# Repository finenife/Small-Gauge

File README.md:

# Small Gauge
 Open Source replacement for the Mazda Miata Oil Pressure Gauge 

## some small notes for myself of other repos ill be referencing
- ill likely move this away from a mono repo at some point

- Screen - ST77903 - 1.6 Inch TFT Display  LCD MODULE Circular Display 400x400 ST77903 Driver Quad-SPI Interface 14Pins
https://a.aliexpress.com/_mM0T8uA

- LVGL - https://lvgl.io/

- ESP-IDF CAN (TWAI) Library documentation
https://docs.espressif.com/projects/esp-idf/en/stable/esp32s2/api-reference/peripherals/twai.html

- RejsaCAN-ESP32 https://github.com/MagnusThome/RejsaCAN-ESP32

- ST77903 ESP Library
https://github.com/moononournation/Arduino_GFX/issues/395

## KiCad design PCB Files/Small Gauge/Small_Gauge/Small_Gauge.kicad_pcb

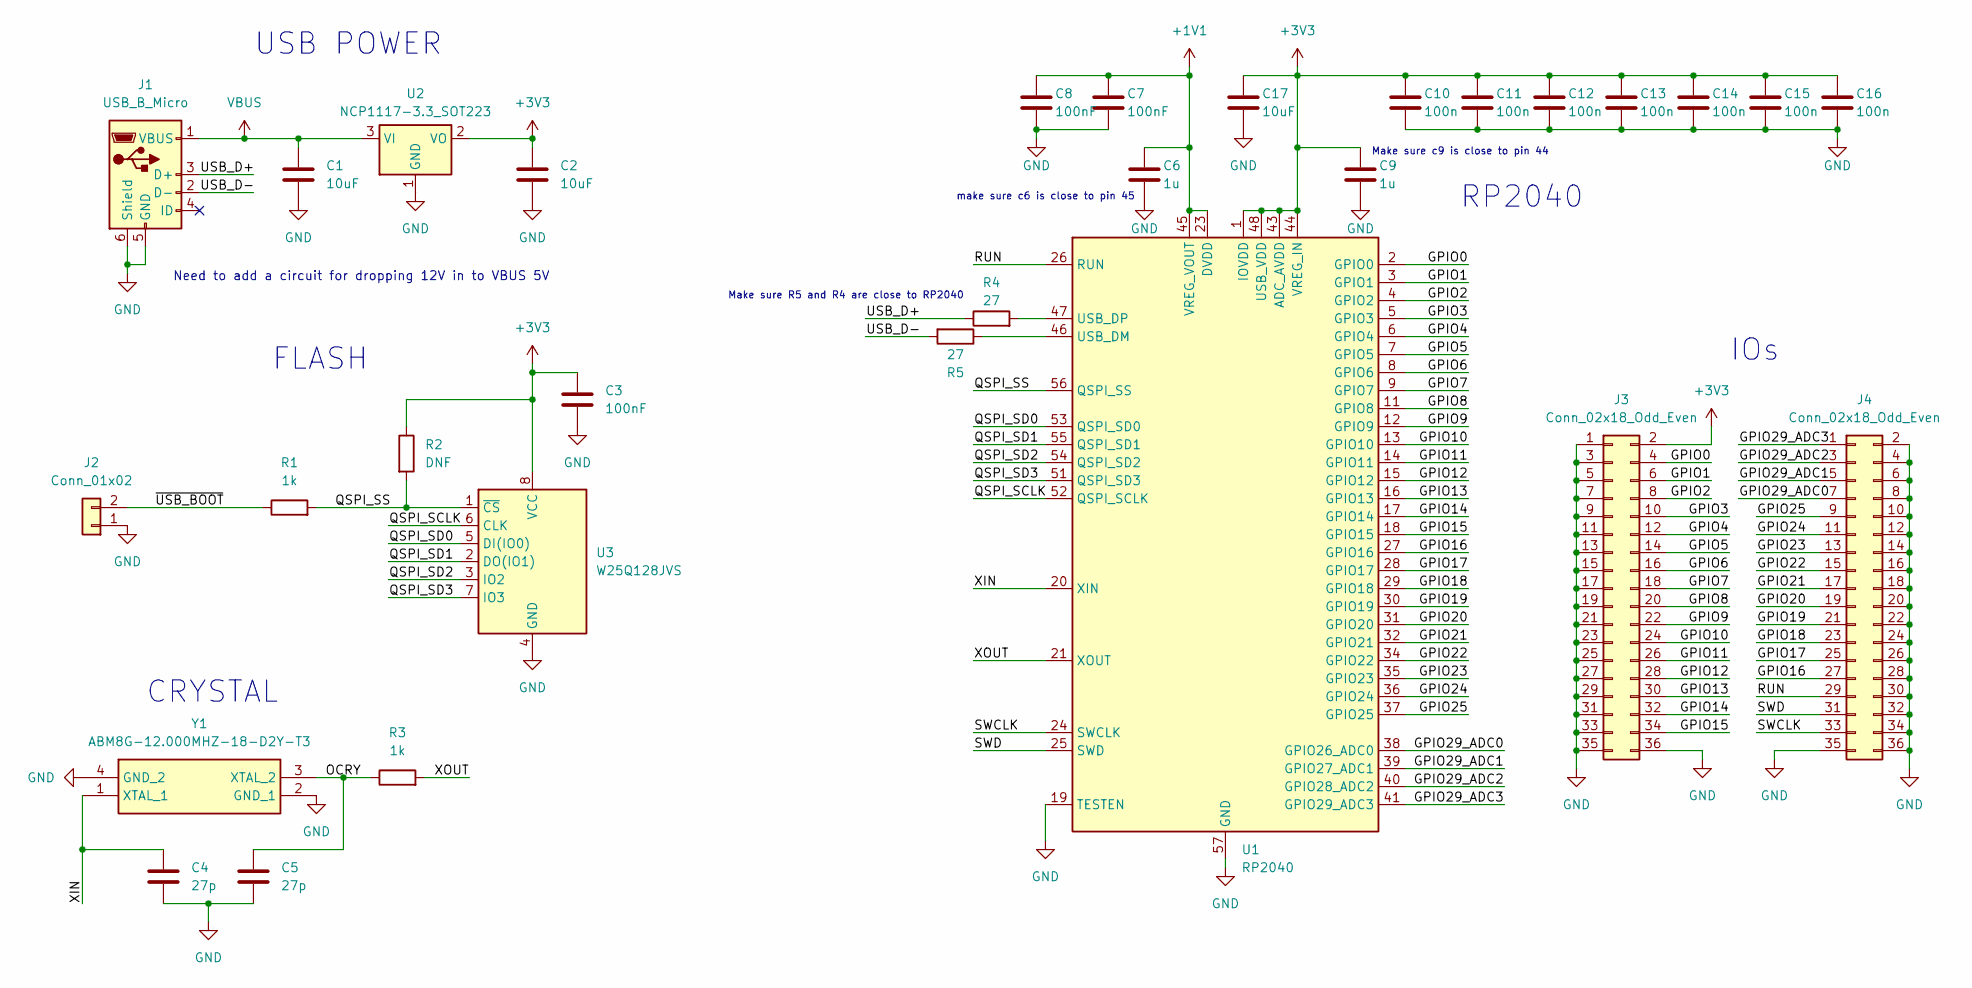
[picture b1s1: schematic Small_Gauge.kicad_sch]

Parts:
C1, C2, C17: 10uF; C_0402_1005Metric_Pad0.74x0.62mm_HandSolder
C3, C7, C8: 100nF; R_0201_0603Metric
C4, C5: 27p; C_0201_0603Metric
C6, C9: 1u; C_0201_0603Metric
C10, C11, C12, C13, C14, C15, C16: 100n; R_0201_0603Metric
J1: USB_B_Micro; USB_MICRO_B_1051640001
J2: Conn_01x02; JST_EH_B2B-EH-A_1x02_P2.50mm_Vertical
J3, J4: Conn_02x18_Odd_Even; JST_PUD_B36B-PUDSS_2x18_P2.00mm_Vertical
R1, R3: 1k; R_0201_0603Metric_Pad0.64x0.40mm_HandSolder
R2: DNF; R_0201_0603Metric_Pad0.64x0.40mm_HandSolder
R4, R5: 27; R_0402_1005Metric
U1: RP2040; QFN-56-1EP_7x7mm_P0.4mm_EP3.2x3.2mm
U2: NCP1117-3.3_SOT223; SOT-223-3_TabPin2
U3: W25Q128JVS; SOIC-8_5.23x5.23mm_P1.27mm
Y1: ABM8G-12.000MHZ-18-D2Y-T3; ABM8G; Mouser Part Number 815-ABM8G1218D2YT3

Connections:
+1V1: C6.1, C7.1, C8.1, U1.23 (DVDD), U1.45 (VREG_VOUT), U1.50 (DVDD)
+3V3: C2.1, C3.1, C9.1, C10.1, C11.1, C12.1, C13.1, C14.1, C15.1, C16.1, C17.1, J3.2, R2.1, U1.1 (IOVDD), U1.10 (IOVDD), U1.22 (IOVDD), U1.33 (IOVDD), U1.42 (IOVDD), U1.43 (ADC_AVDD), U1.44 (VREG_IN), U1.48 (USB_VDD), U1.49 (IOVDD), U2.2 (VO), U3.8 (VCC)
/GPIO0: J3.4, U1.2 (GPIO0)
/GPIO1: J3.6, U1.3 (GPIO1)
/GPIO2: J3.8, U1.4 (GPIO2)
/GPIO3: J3.10, U1.5 (GPIO3)
/GPIO4: J3.12, U1.6 (GPIO4)
/GPIO5: J3.14, U1.7 (GPIO5)
/GPIO6: J3.16, U1.8 (GPIO6)
/GPIO7: J3.18, U1.9 (GPIO7)
/GPIO8: J3.20, U1.11 (GPIO8)
/GPIO9: J3.22, U1.12 (GPIO9)
/GPIO10: J3.24, U1.13 (GPIO10)
/GPIO11: J3.26, U1.14 (GPIO11)
/GPIO12: J3.28, U1.15 (GPIO12)
/GPIO13: J3.30, U1.16 (GPIO13)
/GPIO14: J3.32, U1.17 (GPIO14)
/GPIO15: J3.34, U1.18 (GPIO15)
/GPIO16: J4.27, U1.27 (GPIO16)
/GPIO17: J4.25, U1.28 (GPIO17)
/GPIO18: J4.23, U1.29 (GPIO18)
/GPIO19: J4.21, U1.30 (GPIO19)
/GPIO20: J4.19, U1.31 (GPIO20)
/GPIO21: J4.17, U1.32 (GPIO21)
/GPIO22: J4.15, U1.34 (GPIO22)
/GPIO23: J4.13, U1.35 (GPIO23)
/GPIO24: J4.11, U1.36 (GPIO24)
/GPIO25: J4.9, U1.37 (GPIO25)
/GPIO29_ADC0: J4.7, U1.38 (GPIO26_ADC0)
/GPIO29_ADC1: J4.5, U1.39 (GPIO27_ADC1)
/GPIO29_ADC2: J4.3, U1.40 (GPIO28_ADC2)
/GPIO29_ADC3: J4.1, U1.41 (GPIO29_ADC3)
/OCRY: C5.1, R3.1, Y1.3 (XTAL_2)
/QSPI_SCLK: U1.52 (QSPI_SCLK), U3.6 (CLK)
/QSPI_SD0: U1.53 (QSPI_SD0), U3.5 (DI(IO0))
/QSPI_SD1: U1.55 (QSPI_SD1), U3.2 (DO(IO1))
/QSPI_SD2: U1.54 (QSPI_SD2), U3.3 (IO2)
/QSPI_SD3: U1.51 (QSPI_SD3), U3.7 (IO3)
/QSPI_SS: R1.2, R2.2, U1.56 (QSPI_SS), U3.1 (~CS)
/RUN: J4.29, U1.26 (RUN)
/SWCLK: J4.33, U1.24 (SWCLK)
/SWD: J4.31, U1.25 (SWD)
/USB_D+: J1.3 (D+), R4.1
/USB_D-: J1.2 (D-), R5.2
/XIN: C4.1, U1.20 (XIN), Y1.1 (XTAL_1)
/XOUT: R3.2, U1.21 (XOUT)
/~USB_BOOT: J2.2, R1.1
GND: C1.2, C2.2, C3.2, C4.2, C5.2, C6.2, C7.2, C8.2, C9.2, C10.2, C11.2, C12.2, C13.2, C14.2, C15.2, C16.2, C17.2, J1.5 (GND), J1.6 (Shield), J2.1, J3.1, J3.3, J3.5, J3.7, J3.9, J3.11, J3.13, J3.15, J3.17, J3.19, J3.21, J3.23, J3.25, J3.27, J3.29, J3.31, J3.33, J3.35, J3.36, J4.2, J4.4, J4.6, J4.8, J4.10, J4.12, J4.14, J4.16, J4.18, J4.20, J4.22, J4.24, J4.26, J4.28, J4.30, J4.32, J4.34, J4.35, J4.36, U1.19 (TESTEN), U1.57 (GND), U2.1 (GND), U3.4 (GND), Y1.2 (GND_1), Y1.4 (GND_2)
unnamed: R5.1, U1.46 (USB_DM)
unnamed: R4.2, U1.47 (USB_DP)
VBUS: C1.1, J1.1 (VBUS), U2.3 (VI)

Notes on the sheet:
CRYSTAL
Make sure R5 and R4 are close to RP2040
RP2040
make sure c6 is close to pin 45
IOs
FLASH
Need to add a circuit for dropping 12V in to VBUS 5V
USB POWER
Make sure c9 is close to pin 44

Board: 2 copper layers, 28 parts (0 on the bottom side), 18 nets, no tracks yet.

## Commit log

2023-10-11 Initial Commit
    Initial Project Organization Start
2023-10-11 Gauge Render Idea
    A quick render of what the gauge might look like
2023-10-12 initial renderings
2023-10-17 making the factory oil gauge
2023-10-19 some screen updates
2023-11-02 datashit
2023-11-03 micro usb part
2023-11-07 first pcb commit
2024-01-27 frame objects
2024-03-12 initial st77903 w/ lvgl demo
    adding initial working st77903 esp32-s3 code with lvgl demo
2024-03-12 Initial Gauge Animation
    Gauge Working
2024-03-16 no text on screen now
2024-03-19 KiCad ESP 32 stuff
